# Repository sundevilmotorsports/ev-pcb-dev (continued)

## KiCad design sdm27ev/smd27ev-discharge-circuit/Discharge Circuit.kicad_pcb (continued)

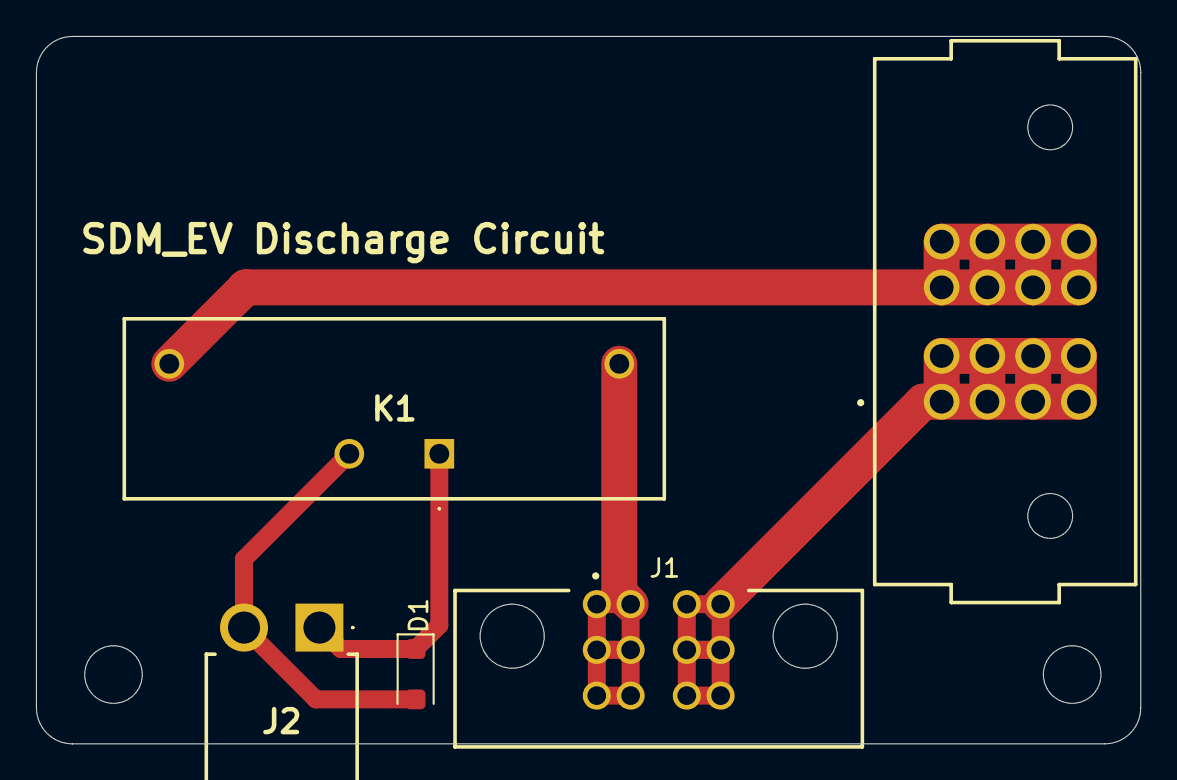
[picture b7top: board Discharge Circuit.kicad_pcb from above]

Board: 2 copper layers, 61.3 x 39.3 mm, 7 parts (0 on the bottom side), 5 nets.
